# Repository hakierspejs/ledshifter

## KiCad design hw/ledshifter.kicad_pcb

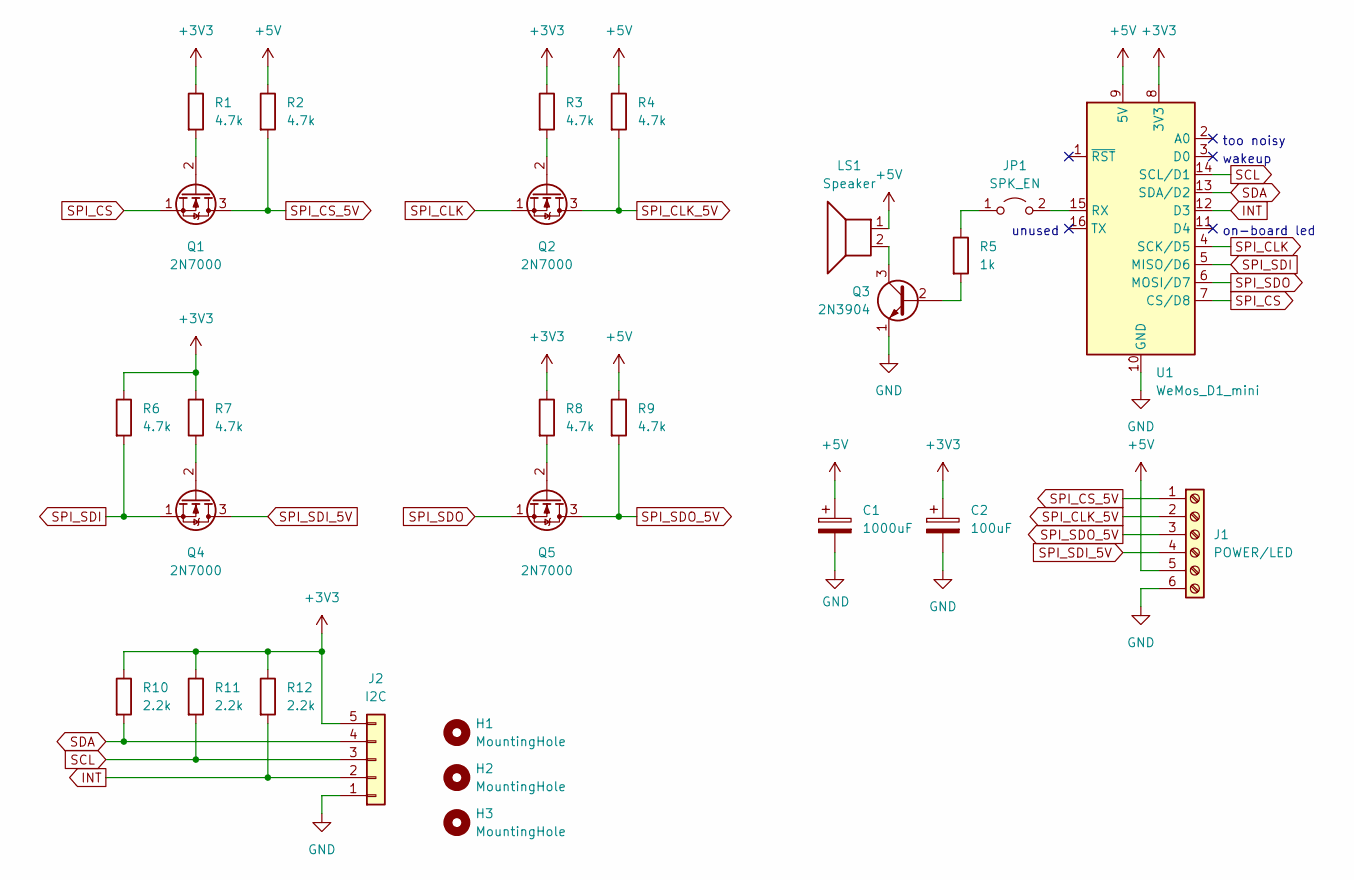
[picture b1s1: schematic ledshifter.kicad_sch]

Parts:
C1: 1000uF; CP_Radial_D10.0mm_P5.00mm
C2: 100uF; CP_Radial_D5.0mm_P2.50mm
H1, H2, H3: MountingHole; MountingHole_3.2mm_M3
J1: POWER/LED; TerminalBlock_MetzConnect_Type011_RT05506HBWC_1x06_P5.00mm_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
J2: I2C; PinHeader_1x05_P2.54mm_Vertical
JP1: SPK_EN; TestPoint_2Pads_Pitch2.54mm_Drill0.8mm
LS1: Speaker; TerminalBlock_MetzConnect_Type011_RT05502HBWC_1x02_P5.00mm_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
Q1, Q2, Q4, Q5: 2N7000; TO-92_Inline
Q3: 2N3904; TO-92_Inline
R1, R2, R3, R4, R6, R7, R8, R9: 4.7k; R_Axial_DIN0204_L3.6mm_D1.6mm_P5.08mm_Horizontal
R5: 1k; R_Axial_DIN0204_L3.6mm_D1.6mm_P5.08mm_Horizontal
R10, R11, R12: 2.2k; R_Axial_DIN0204_L3.6mm_D1.6mm_P5.08mm_Horizontal
U1: WeMos_D1_mini; WEMOS_D1_mini_light

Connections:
+3V3: C2.1, J2.5, R1.1, R3.1, R6.1, R7.2, R8.1, R10.1, R11.1, R12.1, U1.8 (3V3)
+5V: C1.1, J1.5, LS1.1, R2.1, R4.1, R9.1, U1.9 (5V)
GND: C1.2, C2.2, J1.6, J2.1, Q3.1 (E), U1.10 (GND)
INT: J2.2, R12.2, U1.12 (D3)
unnamed: JP1.1 (A), R5.1
unnamed: JP1.2 (B), U1.15 (RX)
unnamed: LS1.2, Q3.3 (C)
unnamed: Q1.2 (G), R1.2
unnamed: Q2.2 (G), R3.2
unnamed: Q3.2 (B), R5.2
unnamed: Q5.2 (G), R8.2
unnamed: Q4.2 (G), R7.1
SCL: J2.3, R11.2, U1.14 (SCL/D1)
SDA: J2.4, R10.2, U1.13 (SDA/D2)
SPI_CLK: Q2.1 (S), U1.4 (SCK/D5)
SPI_CLK_5V: J1.2, Q2.3 (D), R4.2
SPI_CS: Q1.1 (S), U1.7 (CS/D8)
SPI_CS_5V: J1.1, Q1.3 (D), R2.2
SPI_SDI: Q4.1 (S), R6.2, U1.5 (MISO/D6)
SPI_SDI_5V: J1.4, Q4.3 (D)
SPI_SDO: Q5.1 (S), U1.6 (MOSI/D7)
SPI_SDO_5V: J1.3, Q5.3 (D), R9.2

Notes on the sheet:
on-board led
unused
too noisy
wakeup

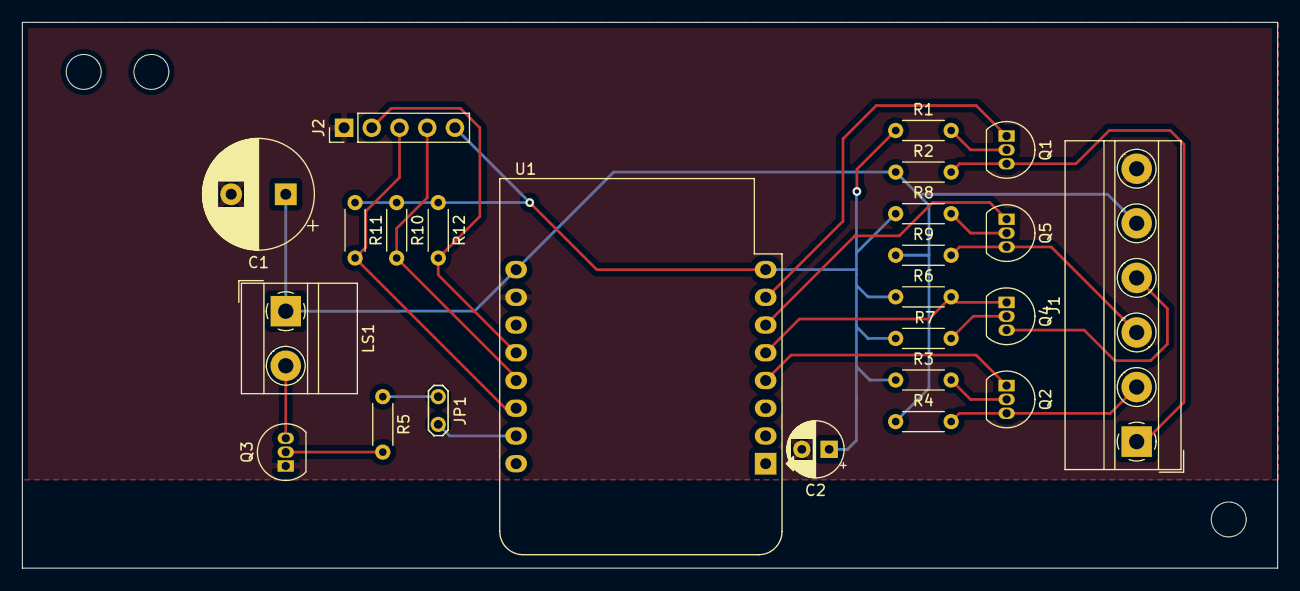
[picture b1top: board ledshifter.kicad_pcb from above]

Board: 2 copper layers, 115.0 x 50.0 mm, 27 parts (0 on the bottom side), 22 nets.
